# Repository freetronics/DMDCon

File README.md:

Freetronics DMDCon
==============================
Copyright 2011-2014 Freetronics Pty Ltd
Freetronics site:  http://www.freetronics.com/

An adapter board to connect an Arduino (or compatible) board to a
Freetronics Dot Matrix Display 32x16 pixel LED matrix.

DMD displays:
http://www.freetronics.com/collections/display/dmd

INSTALLATION
------------
The design is saved as an EAGLE project. EAGLE PCB design software is
available from www.cadsoftusa.com free for non-commercial use. To use
this project download it and place the directory containing these files
into the "eagle" directory on your computer. Then open EAGLE and
navigate to Projects -> eagle -> ProtoShieldShort.

DISTRIBUTION
------------
The specific terms of distribution of this project are governed by the
license referenced below.

LICENSE
-------
Licensed under the TAPR Open Hardware License (http://www.tapr.org/OHL).
The LICENSE file within this repository contains a copy of
this license in plain text format.

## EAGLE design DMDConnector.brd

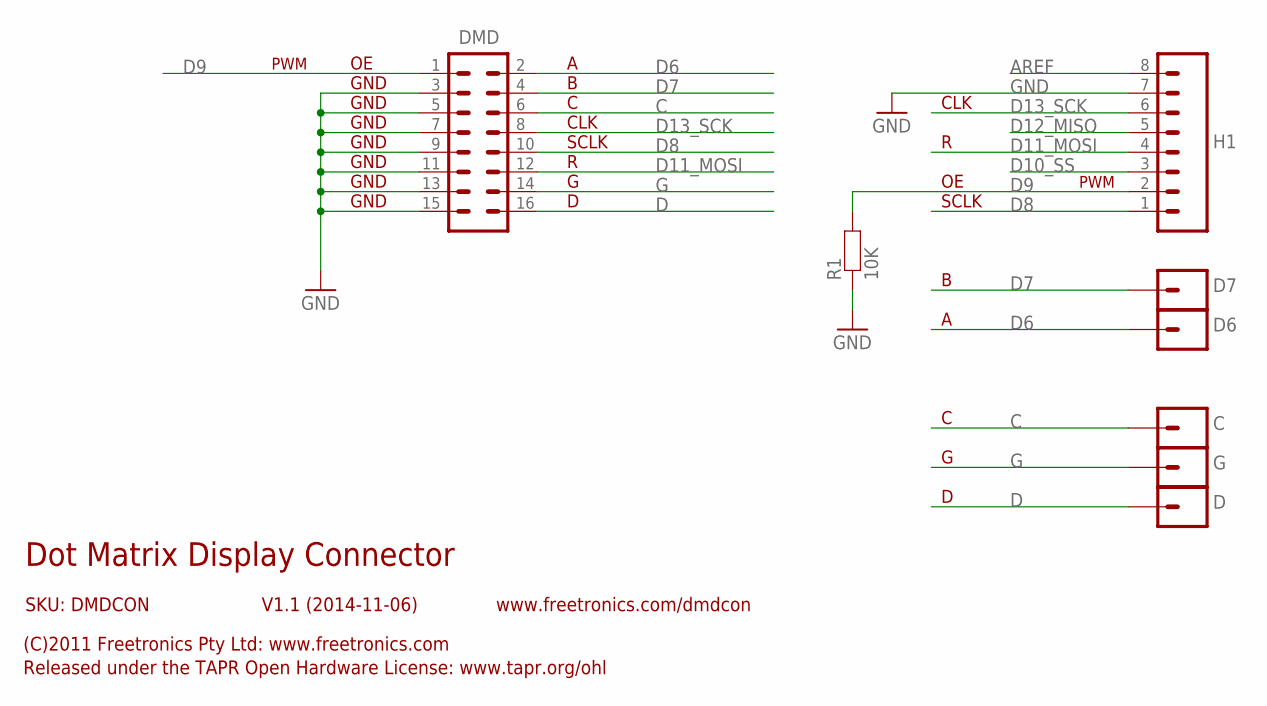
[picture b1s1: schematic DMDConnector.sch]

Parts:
C: M01PTH; 1X01
D, D6, D7: M01PTH; 1X01
DMD: M08X2; 2X8-SMALLERPADS
G: M01PTH; 1X01
H1: Digital_8_13; 1X08
R1: 10K; 0805

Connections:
AREF: H1.8
C: C.1, DMD.6
D: D.1, DMD.16
D6: D6.1, DMD.2
D7: D7.1, DMD.4
D8: DMD.10, H1.1
D9: DMD.1, H1.2, R1.2
D10_SS: H1.3
D11_MOSI: DMD.12, H1.4
D12_MISO: H1.5
D13_SCK: DMD.8, H1.6
G: DMD.14, G.1
GND: DMD.3, DMD.5, DMD.7, DMD.9, DMD.11, DMD.13, DMD.15, H1.7, R1.1

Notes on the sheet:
Dot Matrix Display Connector
V1.1 (2014-11-06)
SKU: DMDCON
(C)2011 Freetronics Pty Ltd: www.freetronics.com
Released under the TAPR Open Hardware License: www.tapr.org/ohl
www.freetronics.com/dmdcon
GND
CLK
SCLK
PWM

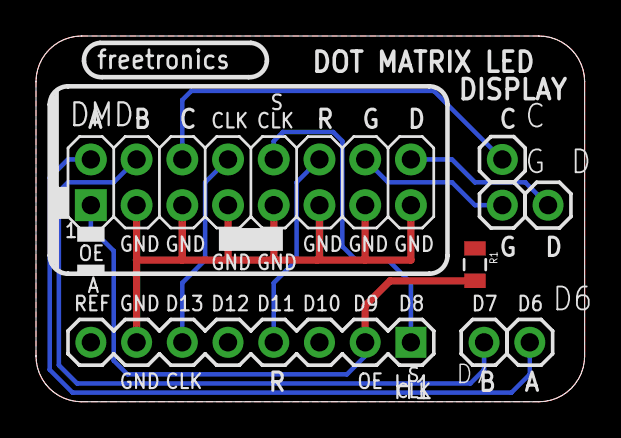
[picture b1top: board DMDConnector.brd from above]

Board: 2 copper layers, 30.5 x 20.3 mm, 8 parts (0 on the bottom side), 10 nets.

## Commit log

2014-11-06 Belated git import
2014-11-06 Update to Eagle 6 format
2014-11-06 Rename nOE line to OE, add pulldown resistor, bump version to V1.1
2014-11-06 Regenerate PDF
2014-11-10 Minor cosmetic tweaks for V1.1 production files

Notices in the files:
DMDConnector.brd:
(C)2014 Freetronics Pty Ltd
